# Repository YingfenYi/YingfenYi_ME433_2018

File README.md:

# YingfenYi_ME433_2018
Creator: Yingfen Yi  
Date: Apr - Jun 2018

This is a project repository for ME433.

Each homework is a step toward the final Automated Guided Vehicle/ Auto-tracking Wheeled Robot.

HW1 is initial PIC32 circuit design and construction on breadboard.

HW2-3 is learning and using Eagle to do PCB design.

HW4 is DAC(Digital signal to Analog signal Convertor) based on SPI communication.

HW5 is a light switch based on I2C communication.

HW6-7 is to read accelerometer data  from IMU then accordingly show the orientation of the board with a crossform slidebar on LCD screen.

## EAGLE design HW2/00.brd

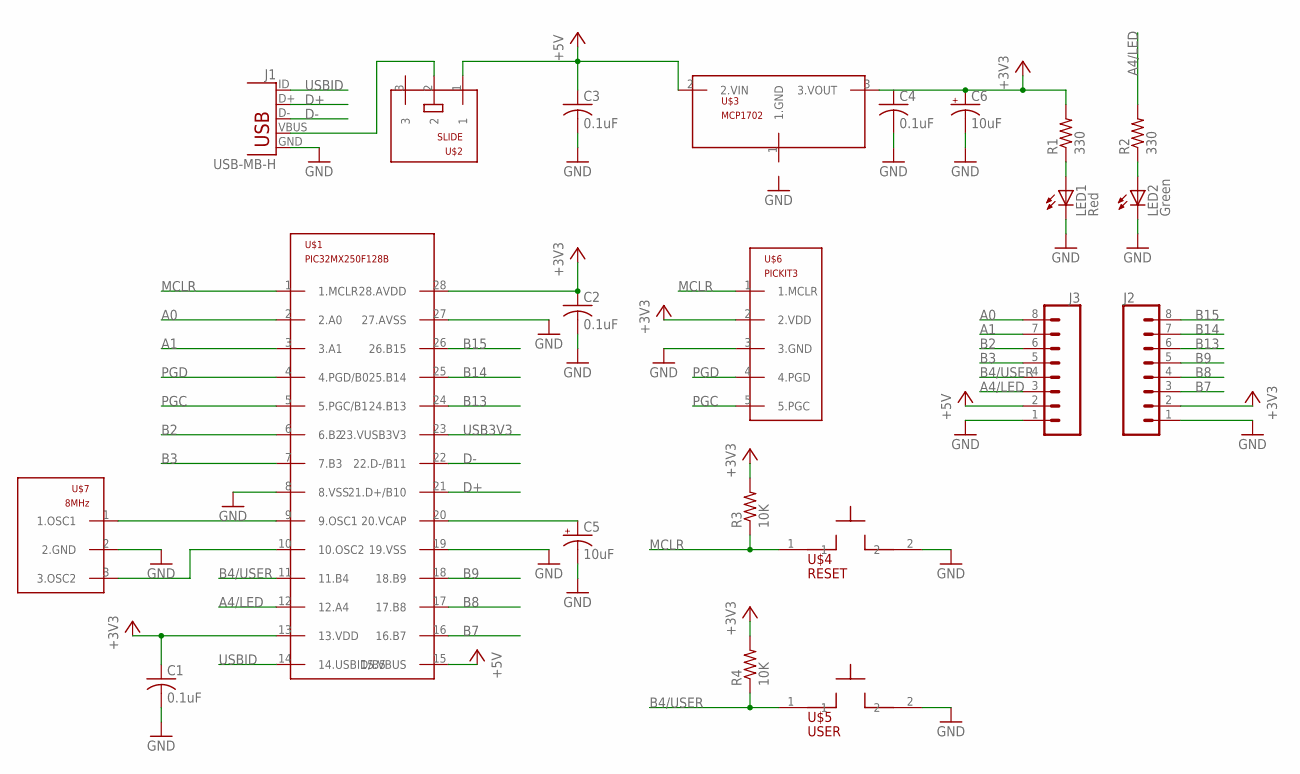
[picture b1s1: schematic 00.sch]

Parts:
C1, C2, C3, C4: 0.1uF; C025-025X050
C5, C6: 10uF; B45181B
J1: USB-MB-H
J2, J3: CONN_08"; 1X08
LED1: Red; LED3MM
LED2: Green; LED3MM
R1, R2: 330; 0207/10
R3, R4: 10K; 0207/10
U$1: PIC32MX250F128B; DIL28-3
U$2: SLIDE
U$3: MCP1702; TO92
U$4: RESET; PB
U$5: USER; PB
U$6: PICKIT3; 1X05
U$7: 8MHz; OSC

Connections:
+3V3: C1.1, C2.1, C6.+, J2.2, R1.2, R3.2, R4.2, U$1.13 (13.VDD), U$1.28 (28.AVDD), U$3.3 (3.VOUT), U$6.2 (2.VDD)
+5V: C3.1, J3.2, U$1.15 (15.VBUS), U$2.1, U$3.2 (2.VIN)
A0: J3.8, U$1.2 (2.A0)
A1: J3.7, U$1.3 (3.A1)
A4/LED: J3.3, R2.2, U$1.12 (12.A4)
B2: J3.6, U$1.6 (6.B2)
B3: J3.5, U$1.7 (7.B3)
B4/USER: J3.4, R4.1, U$1.11 (11.B4), U$5.1
B7: J2.3, U$1.16 (16.B7)
B8: J2.4, U$1.17 (17.B8)
B9: J2.5, U$1.18 (18.B9)
B13: J2.6, U$1.24 (24.B13)
B14: J2.7, U$1.25 (25.B14)
B15: J2.8, U$1.26 (26.B15)
D+: J1.D+, U$1.21 (21.D+/B10)
D-: J1.D-, U$1.22 (22.D-/B11)
GND: C1.2, C2.2, C3.2, C4.2, C5.-, C6.-, J1.GND, J2.1, J3.1, LED1.K (C), LED2.K (C), U$1.8 (8.VSS), U$1.19 (19.VSS), U$1.27 (27.AVSS), U$4.2, U$5.2, U$6.3 (3.GND), U$7.2 (2.GND)
MCLR: R3.1, U$1.1 (1.MCLR), U$4.1, U$6.1 (1.MCLR)
unnamed: LED2.A, R2.1
unnamed: J1.VBUS, U$2.2
unnamed: LED1.A, R1.1
unnamed: U$1.9 (9.OSC1), U$7.1 (1.OSC1)
unnamed: U$1.10 (10.OSC2), U$7.3 (3.OSC2)
unnamed: C5.+, U$1.20 (20.VCAP)
PGC: U$1.5 (5.PGC/B1), U$6.5 (5.PGC)
PGD: U$1.4 (4.PGD/B0), U$6.4 (4.PGD)
USB3V3: U$1.23 (23.VUSB3V3)
USBID: J1.ID, U$1.14 (14.USBID/B5)

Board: 2 copper layers, 22 parts (0 on the bottom side), 27 nets, no tracks yet.

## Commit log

2018-04-08 Create README.md
    My first commit!
2018-04-09 First draft of code
2018-04-09 ver2
2018-04-09 IDE project
2018-04-10 picture added
2018-04-10 ver 3
2018-05-07 HW6-9
2018-05-08 HW1 revision
2018-05-08 HW5 revision1
2018-05-08 hw5 re2
2018-05-09 HW4 re1
2018-05-09 hw4 re2
2018-05-09 hw4 re3
2018-05-16 video
2018-05-17 hw12
2018-05-18 hw13
2018-05-18 hw6 improvement
2018-05-22 hw7 almost done
2018-05-22 hw1 slightly change
2018-05-22 hw7 revision
2018-05-24 hw13 and 14
2018-06-04 hw15
2018-06-04 hw10
2018-06-04 hw11
2018-06-06 hw14
2018-06-06 android part fin
2018-06-08 hw7 demolink
2018-06-08 hw9 fin
2018-06-12 HW16
2018-06-12 hw17
2018-06-14 hw17 clear
2018-06-14 hw18
2018-06-14 photos and demolink attached
2018-06-26 update the description
2019-06-04 add exported schematic diagram
